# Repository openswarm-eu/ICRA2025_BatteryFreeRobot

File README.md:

# ICRA2025_Battery-Free Robot CapBot 

## Abstract

> Swarm robotics focuses on designing and coordinating large groups of relatively simple robots to perform tasks in a decentralised and collective manner.
> The swarm provides a resilient and flexible solution for many applications.
> However, contemporary swarm robots have a significant power problem in that secondary (i.e. rechargeable) batteries are slow to charge and offer lifetimes of only a few years, increasing maintenance costs and pollution due to battery replacement.
> We imagine a different future, wherein battery-free robots powered by supercapacitors can be recharged in seconds, offer long-life autonomous operation and can rapidly pass charge between one another using trophallaxis.
> In pursuit of this vision, we contribute the _CapBot_, a battery-free swarm robot equipped with Mecanum wheels, a Cortex-M4F application processor and Bluetooth Low Energy networking.
> CapBot  fully recharges in 16 s, offers 51 min of autonomous operation at top speed, and can transfer up to 50% of its available charge to a peer via trophallaxis in under 20 s.
> It is fully open-source: all software and hardware sources are available in this repository.

## Artefacts

### Hardware

CapBot's hardware is designed using KiCad, the design files are provided under [Hardware_Design](./Hardware_Design).

### Software

The [Software_Design](./Software_Design) folder contains an example using the CapBot Zephyr API.
The library itself is hosted at our [GitLab instance](https://gitlab.kuleuven.be/distrinet/taskforces/nes/capbot) and is included in this example using git submodules.

# CapBot ICRA demo

Fetch submodules:
```sh
git submodule update --init
```
Open workspace in [Visual Studio Code](https://code.visualstudio.com/):
```sh
code Software_Design
```
Make sure that the nRF Connect extension is installed according to the instructions at [Nordic's DevAcademy](https://academy.nordicsemi.com/courses/nrf-connect-sdk-fundamentals/lessons/lesson-1-nrf-connect-sdk-introduction/topic/exercise-1-1/)
Now, you should be able to open an nRF Connect terminal in Visual Studio Code. 
Next, execute [west](https://docs.nordicsemi.com/bundle/ncs-latest/page/zephyr/develop/west/index.html):
```sh
west build --build-dir build --board freebot-nrf52840 . -- -DBOARD_ROOT=.
```
This builds the demo project and creates a binary at `build/zephyr/zephyr.elf`.
[PyOCD](https://pyocd.io/) can then be used to flash the binary to the robot:
```sh
pyocd load -t nrf52840 build/zephyr/zephyr.hex
```

# Acknowledgement

Part of the source code in this repository is developed within the frame and for the purpose of the OpenSwarm project. This project has received funding from the European Unioan's Horizon Europe Framework Programme under Grant Agreement No. 101093046.

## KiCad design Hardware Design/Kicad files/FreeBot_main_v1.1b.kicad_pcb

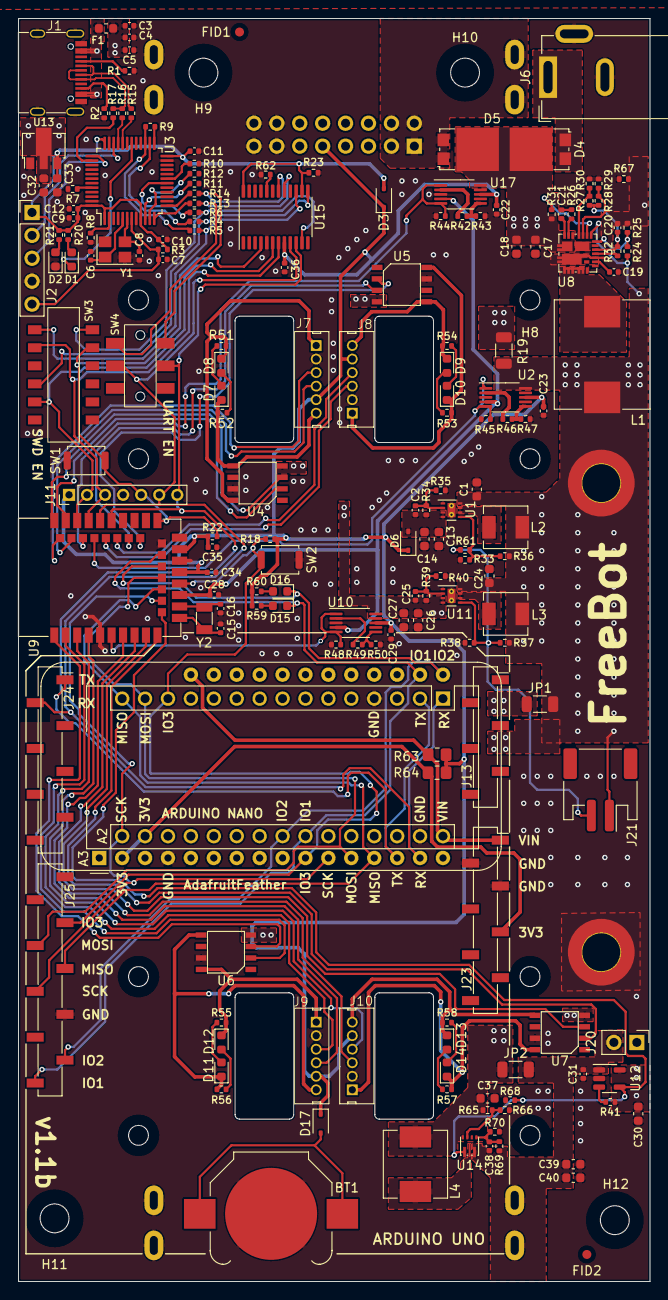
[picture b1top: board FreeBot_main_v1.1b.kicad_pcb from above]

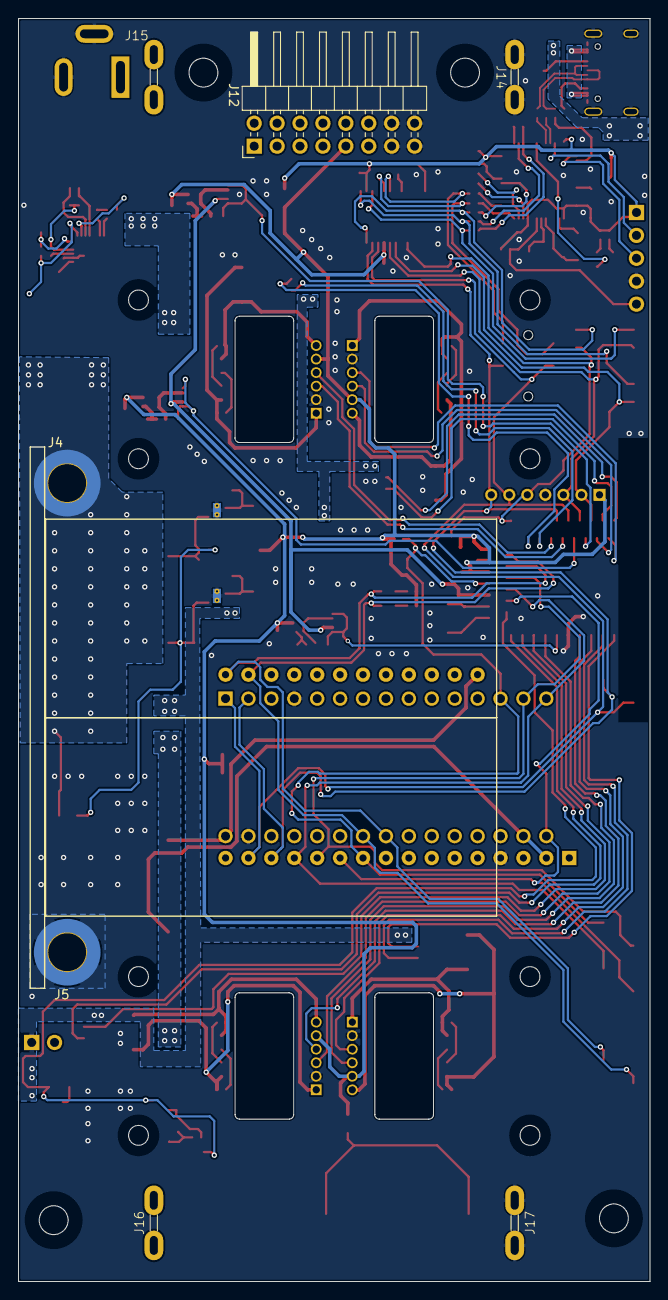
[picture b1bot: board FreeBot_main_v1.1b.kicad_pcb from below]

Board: 2 copper layers, 70.0 x 140.0 mm, 194 parts (7 on the bottom side), 126 nets.

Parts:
A2: Arduino_Nano_v3.x; Arduino_Nano
A3: Adafruit_Feather_Generic; Adafruit_Feather
BT1: Battery_Cell; BatteryHolder_Keystone_3000_1x12mm
C1, C24, C30, C32, C33, C37: 10uF; C_0603_1608Metric
C2, C25, C38: 10pF; C_0402_1005Metric
C3, C4, C5, C20: 1uF; C_0402_1005Metric
C6, C8: 22p; C_0402_1005Metric
C7, C9, C10, C11, C12, C21, C22, C23, C29, C31, C34, C35, C36: 0.1uF; C_0402_1005Metric
C13, C14, C17, C18, C26, C27, C39, C40: 22uF; C_0603_1608Metric
C15, C16: 12pF; C_0402_1005Metric
C19: 2.2uF; C_0402_1005Metric
C28: 0.01uF; C_0402_1005Metric
D1: Red; LED_0603_1608Metric
D2: Green; LED_0603_1608Metric
D3, D6, D17: CUS10S30,H3F; D_SOD-323
D4, D5: 10S45SP; TO-277A
D7, D10, D11, D14: GREEN LED NCD0603G1; LED_0603_1608Metric
D8, D9, D12, D13: RED LED NCD0603R1; LED_0603_1608Metric
D15, D16: 19-217/BHC-ZL1M2RY/3T; LED_0603_1608Metric
F1: S1206-F-6.0A; Fuse_0603_1608Metric
FID1, FID2: Fiducial; Fiducial_1mm_Mask2mm
H1, H2, H3, H4, H5, H6, H7, H8: MountingHole; MountingHole_2.2mm_M2_ISO7380
H9, H10, H11, H12: MountingHole; MountingHole_3.2mm_M3_ISO14580
J1: USB-type-c-16p; TYPE-C-31-M-12
J2: Conn_01x05; PinHeader_1x05_P2.54mm_Vertical
J4, J5: Conn_01x01; MountingHole_3.2mm_M3_Pad_TopBottom
J6: Barrel_Jack_MountingPin; BarrelJack_GCT_DCJ200-10-A_Horizontal
J7, J8, J9, J10: Conn_01x06; ZH-1.5mm-1x6p-TH
J11: Conn_01x07; PinHeader_1x07_P2.00mm_Vertical
J12: Conn_02x08_Odd_Even; PinHeader_2x08_P2.54mm_Horizontal
J13: Conn_01x06; PinSocket_1x06_P2.54mm_Vertical_SMD_Pin1Right
J14, J16: Conn_01x01; M3-side-terminal-DZ-32
J15, J17: Conn_01x01; M3-side-terminal-DZ-43
J20: Conn_01x02; PinHeader_1x02_P2.54mm_Vertical
J21: Conn_01x02; JST_PH_S2B-PH-SM4-TB_1x02-1MP_P2.00mm_Horizontal
J23, J24: Conn_01x08; PinSocket_1x08_P2.54mm_Vertical_SMD_Pin1Right
J25: Conn_01x10; PinSocket_1x10_P2.54mm_Vertical_SMD_Pin1Right
JP1, JP2: SolderJumper_2_Open; R_1206_3216Metric
L1: 300nH; L_Chilisin_BMRF00101040
L2, L3: 470nH FXL0420-R47-M; L_Sunlord_MWSA0412S
L4: 1uH FXL0630-1R0-M; L_Sunlord_MWSA0603S
R1, R2: 5.1k; R_0402_1005Metric
R3, R7, R18, R22, R27, R31, R32, R35, R36, R38, R40, R41, R44, R45, R48, R68, R70: 100k; R_0402_1005Metric
R4, R5, R6, R11, R12, R13, R14, R15, R16: 22; R_0402_1005Metric
R8: 10k DNP; R_0402_1005Metric
R9, R20, R52, R53, R56, R57, R59, R60: 100; R_0402_1005Metric
R10, R62, R66: 0; R_0402_1005Metric
R17: 1.5k; R_0402_1005Metric
R19: DNP; R_1206_3216Metric
R21, R51, R54, R55, R58: 27; R_0402_1005Metric
R23, R25, R43, R47, R50: 10k; R_0402_1005Metric
R24: 36.5k; R_0402_1005Metric
R26, R67: 1; R_0402_1005Metric
R28: 499k; R_0402_1005Metric
R29, R30, R33, R37, R61, R65: DNP; R_0402_1005Metric
R34: 348k; R_0402_1005Metric
R39: 316k; R_0402_1005Metric
R42, R46, R49: 390k; R_0402_1005Metric
R63, R64: R; R_0805_2012Metric_Pad1.20x1.40mm_HandSolder
R69: 806k; R_0402_1005Metric
SW1, SW2: TS-1088-AR02016; SW_Push_SPST_NO_Alps_SKRK
SW3: 4PDT-K3-2268S-F1
SW4: Switch-DPDT; DPDT-K3-2235S-F1
U1, U11: WSON-8-1EP_2x2mm_P0.5mm_EP0.9x1.6mm_ThermalVias
U2, U10, U17: TS5A23159DGS; VSSOP-10_3x3mm_P0.5mm
U3: STM32F103CBTx; LQFP-48_7x7mm_P0.5mm
U4, U5, U6, U7: BDR6120H; motor-driver-BDR6120H
U8: SIC431AED-T1-GE3; MLP44-24L SiC431
U9: E73-2G4M08S1C
U12: RT9742AGJ5F; TSOT-23-5
U13: HT7536-1; SOT-89-3
U14: boost-TPS61022; VQFN-HR-7 TPS61022
U15: TS3A27518EPW; TSSOP-24_4.4x7.8mm_P0.65mm
Y1: Crystal_GND24; Crystal_SMD_3225-4Pin_3.2x2.5mm
Y2: Q13FC1350000400; Crystal_SMD_3215-2Pin_3.2x1.5mm

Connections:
/USB-VDD: C9.1, C10.1, C11.1, C12.1, C33.1, D3.2 (A), J2.1, R3.2, R20.1, R21.1, R23.1, U3.1 (VBAT), U3.9 (VDDA), U3.24 (VDD), U3.36 (VDD), U3.48 (VDD), U13.3 (VOUT), U15.14 (IN2), U15.24 (IN1)
/Vbotin: D5.1 (A), D5.2 (A), J12.1, J12.2, J12.3, J12.4, J15.1
/Vbotout: C31.2, C38.2, C39.1, C40.1, J16.1, J20.2, JP2.2 (B), R69.1, U12.1 (VOUT), U14.3 (VOUT)
/Vmotor: C25.2, C26.1, C27.1, C30.1, J20.1, JP1.2 (B), R39.1, R41.1, U4.4 (VDD), U5.4 (VDD), U6.4 (VDD), U7.4 (VDD), U10.10, U11.3 (VOUT), U11.4 (VOUT), U12.5 (VIN)
/add-on-board/3V3: A2.17 (3V3), A3.2 (3V3), J23.5, R64.2
/add-on-board/VIN: A2.30 (VIN), A3.28 (VBAT), J23.1, R63.2
/add-on-board/addon-io.1: A2.24 (A5), A3.18 (SCL), D15.1 (K), J25.10, U9.22 (P0.07)
/add-on-board/addon-io.2: A2.23 (A4), A3.17 (SDA), D16.1 (K), J25.9, U9.20 (P0.12)
/add-on-board/addon-io.3: A2.13 (D10), A3.10 (A5), J25.3, R18.2, SW2.2, U9.17 (P1.09)
/add-on-board/addon-spi.miso: A2.15 (D12), A3.13 (MISO), J25.5, U9.16 (P0.08)
/add-on-board/addon-spi.mosi: A2.14 (D11), A3.12 (MOSI), J25.4, U9.18 (P0.04/AIN2)
/add-on-board/addon-spi.sck: A2.16 (D13), A3.11 (SCK), J25.6, U9.14 (P0.06)
/add-on-board/uart.rx: A2.1 (D1/TX), A3.15 (TX), J11.6, J24.2, SW4.5, U9.35 (P0.24), U15.9 (COM4)
/add-on-board/uart.tx: A2.2 (D0/RX), A3.14 (RX), J11.7, J24.1, SW4.2, U9.33 (P0.13), U15.10 (COM5)
/daplink/dap-inner-usb_N: R15.2, U3.32 (PA11)
/daplink/dap-inner-usb_P: R16.2, U3.33 (PA12)
/daplink/dap-led-red: D1.1 (K), U3.30 (PA9)
/daplink/dap-nrst: C7.1, J2.5, R3.1, U3.7 (NRST)
/daplink/dap-swclk: J2.3, U3.37 (PA14)
/daplink/dap-swdio: J2.2, U3.34 (PA13)
/daplink/dap-usbd_N: J1.A7 (DN1), J1.B7 (DN2), R15.1
/daplink/dap-usbd_P: J1.A6 (DP1), J1.B6 (DP2), R16.1, R17.2
/daplink/tgt-rx-dap: R13.2, SW4.4, U15.17 (NO4)
/daplink/tgt-swd-clk-dap: R4.1, SW3.10, U15.13 (NO2)
/daplink/tgt-swd-io-dap: R5.1, SW3.7, U15.15 (NO3)
/daplink/tgt-swd-rst-dap: R6.1, SW3.1, U15.11 (NO1)
/daplink/tgt-swd.clk: J11.2, SW3.11, U9.39 (SWDCLK), U15.6 (COM2)
/daplink/tgt-swd.io: J11.3, SW3.8, U9.37 (SWDIO), U15.7 (COM3)
/daplink/tgt-swd.rst: J11.5, R22.2, SW1.2, SW3.2, U9.26 (P0.18/RESET), U15.4 (COM1)
/daplink/tgt-tx-dap: R14.2, SW4.1, U15.18 (NO5)
/mcu/V-mea: C28.1, U2.4, U9.15 (P0.05/AIN3), U10.4, U17.4
/mcu/Vbotout-EN: R68.1, U9.12 (P0.26), U12.4 (EN), U14.1 (EN)
/mcu/Vcap-mea-en: R45.1, U2.1, U2.5, U9.36 (P1.00/SWO)
/mcu/Vin-mea-en: R44.1, U9.38 (P1.02-LS), U17.1, U17.5
/mcu/Vmotor-mea-en: R48.1, U9.6 (P1.13-LS), U10.1, U10.5
/mcu/m1-ctrl.in-a: U4.2 (INA), U9.41 (P0.09/NFC1-LS)
/mcu/m1-ctrl.in-b: U4.3 (INB), U9.43 (P0.10/NFC2-LS)
/mcu/m1-hall.c1: J7.4, U9.40 (P1.04-LS)
/mcu/m1-hall.c2: J7.3, U9.42 (P1.06-LS)
/mcu/m2-ctrl.in-a: U5.2 (INA), U9.28 (P0.15)
/mcu/m2-ctrl.in-b: U5.3 (INB), U9.30 (P0.17)
/mcu/m2-hall.c1: J8.4, U9.32 (P0.20)
/mcu/m2-hall.c2: J8.3, U9.34 (P0.22)
/mcu/m3-ctrl.in-a: U6.2 (INA), U9.2 (P1.10-LS)
/mcu/m3-ctrl.in-b: U6.3 (INB), U9.1 (P1.11-LS)
/mcu/m3-hall.c1: J9.4, U9.7 (P0.02/AIN1-LS)
/mcu/m3-hall.c2: J9.3, U9.3 (P0.03/AIN1-LS)
/mcu/m4-ctrl.in-a: U7.2 (INA), U9.10 (P0.30/AIN6-LS)
/mcu/m4-ctrl.in-b: U7.3 (INB), U9.9 (P0.31/AIN7-LS)
/mcu/m4-hall.c1: J10.4, U9.4 (P0.28/AIN4-LS)
/mcu/m4-hall.c2: J10.3, U9.8 (P0.29/AIN5-LS)
/pwr1/buck_en: R31.2, U8.19 (EN)
/pwr2/Vbotout-overcurr: R41.2, U12.3 (~FLG)
/pwr2/Vcap: C1.1, C24.1, C37.1, J4.1, J21.1, JP1.1 (A), JP2.1 (A), L1.2, L2.1, L3.1, L4.1, R19.2, R24.1, R36.1, R37.1, R65.1, U1.8 (VIN), U2.10, U8.18 (Vout), U11.8 (VIN), U14.7 (VIN)
/pwr2/Vcap_reg: C2.2, C13.1, C14.1, D6.2 (A), R34.1, U1.3 (VOUT), U1.4 (VOUT)
/pwr2/Vmotor-EN: J21.2, R37.2, R38.1, R61.2, U11.5 (EN)
GND: A2.4 (GND), A2.29 (GND), A3.4 (GND), BT1.2 (-), C1.2, C3.2, C4.2, C5.2, C6.2, C7.2, C8.2, C9.2, C10.2, C11.2, C12.2, C13.2, C14.2, C15.2, C16.2, C17.2, C18.2, C19.2, C20.2, C22.2, C23.2, C24.2, C26.2, C27.2, C28.2, C29.2, C30.2, C31.1, C32.2, C33.2, C34.2, C35.2, C36.1, C37.2, C39.2, C40.2, D2.1 (K), J1.0 (SH), J1.1 (SH), J1.2 (SH), J1.3 (SH), J1.A1 (GND), J1.A12 (GND), J1.B1 (GND), J1.B12 (GND), J2.4, J5.1, J6.2, J6.3 (MP), J7.2, J8.2, J9.2, J10.2, J11.4, J12.13, J12.14, J12.15, J12.16, J14.1, J17.1, J23.2, J23.3, J25.7, R1.2, R2.2, R7.2, R8.1, R10.1, R23.2, R25.2, R29.2, R30.2, R33.2, R35.2, R38.2, R40.2, R43.2, R44.2, R45.2, R47.2, R48.2, R50.2, R62.1, R66.2, R67.1, R67.2, R68.2, R70.2, SW1.1, SW2.1, U1.1 (AGND), U1.9 (PGND), U2.3 (GND), U3.8 (VSSA), U3.23 (VSS), U3.35 (VSS), U3.47 (VSS), U4.7 (GND), U5.7 (GND), U6.7 (GND), U7.7 (GND), U8.3 (Pgnd), U8.4 (Pgnd), U8.13 (Pgnd), U8.16 (Agnd), U8.25 (Agnd), U8.27 (Pgnd), U9.5 (GND), U9.21 (GND), U9.24 (GND), U10.3 (GND), U11.1 (AGND), U11.9 (PGND), U12.2 (GND), U13.1 (GND), U15.5 (GND), U17.3 (GND), Y1.2, Y1.4
unnamed: BT1.1 (+), D17.2 (A)
unnamed: C21.2, R26.2
unnamed: D1.2 (A), R20.2
unnamed: D2.2 (A), R21.2
unnamed: D4.1 (A), D4.2 (A), J6.1
unnamed: C17.1, C18.1, D4.3 (K), D5.3 (K), R19.1, R31.1, U8.1 (Vin), U8.2 (Vin), U8.22 (Vin), U8.26 (Vin), U17.10
unnamed: D7.2 (A), R51.2
unnamed: D7.1 (K), J7.6, R52.2, U4.5 (OUTB)
unnamed: D8.2 (A), R52.1
unnamed: D8.1 (K), J7.1, R51.1, U4.8 (OUTA)
unnamed: D9.2 (A), R53.2
unnamed: D9.1 (K), J8.6, R54.2, U5.5 (OUTB)
unnamed: D10.2 (A), R54.1
unnamed: D10.1 (K), J8.1, R53.1, U5.8 (OUTA)
unnamed: D11.2 (A), R55.2
unnamed: D11.1 (K), J9.6, R56.2, U6.5 (OUTB)
unnamed: D12.2 (A), R56.1
unnamed: D12.1 (K), J9.1, R55.1, U6.8 (OUTA)
unnamed: D13.2 (A), R57.2
unnamed: D13.1 (K), J10.6, R58.2, U7.5 (OUTB)
unnamed: D14.2 (A), R58.1
unnamed: D14.1 (K), J10.1, R57.1, U7.8 (OUTA)
unnamed: D15.2 (A), R59.2
unnamed: D16.2 (A), R60.2
unnamed: F1.1, J1.A4 (VBUS), J1.A9 (VBUS), J1.B4 (VBUS), J1.B9 (VBUS)
unnamed: J1.A5 (CC1), R1.1
unnamed: J1.B5 (CC2), R2.1
unnamed: L1.1, U8.5 (SW), U8.6 (SW), U8.7 (SW), U8.8 (SW), U8.9 (SW)
unnamed: L2.2, U1.6 (SW), U1.7 (SW)
unnamed: L3.2, U11.6 (SW), U11.7 (SW)
unnamed: R42.1, U17.2
unnamed: R42.2, R43.1, U17.6
unnamed: R46.1, U2.2
unnamed: R46.2, R47.1, U2.6
unnamed: R49.1, U10.2
unnamed: R49.2, R50.1, U10.6
unnamed: R33.1, R36.2, R61.1, U1.5 (EN)
unnamed: C2.1, R34.2, R35.1, U1.2 (FB)
unnamed: R7.1, U3.44 (BOOT0)
unnamed: R11.1, U3.10 (PA0)
unnamed: R12.1, U3.11 (PA1)
unnamed: R13.1, U3.12 (PA2)
unnamed: R14.1, U3.13 (PA3)
unnamed: R17.1, U3.38 (PA15)
unnamed: R6.2, U3.18 (PB0)
unnamed: R10.2, U3.19 (PB1)
unnamed: R9.2, U3.25 (PB12)
unnamed: R4.2, U3.26 (PB13)
unnamed: R5.2, R9.1, U3.27 (PB14)
unnamed: R8.2, U3.2 (PC13)
unnamed: C6.1, U3.5 (PD0), Y1.1
unnamed: C8.1, U3.6 (PD1), Y1.3
unnamed: R26.1, U8.23 (BOOT)
unnamed: R24.2, R25.1, U8.17 (FB)
unnamed: R27.2, R30.1, U8.21 (MODE1)
unnamed: R28.2, R29.1, U8.20 (MODE2)
unnamed: C21.1, U8.24 (PHASE)
unnamed: R32.2, U8.14 (Pgood)
unnamed: C20.1, R27.1, R28.1, R32.1, U8.15 (Vdd)
unnamed: C19.1, U8.12 (Vdrv)
unnamed: C15.1, U9.11 (P0.00/XL1), Y2.1
unnamed: C16.1, U9.13 (P0.01/XL2), Y2.2
unnamed: C25.1, R39.2, R40.1, U11.2 (FB)
unnamed: C38.1, R69.2, R70.1, U14.4 (FB)
unnamed: R65.2, R66.1, U14.6 (MODE)
unnamed: L4.2, U14.2 (SW)
unnamed: R62.2, U15.20 (~EN)
VBUS: C3.1, C4.1, C5.1, C32.1, F1.2, U13.2 (VIN)
VDD: C22.1, C23.1, C29.1, C34.1, C35.1, C36.2, D3.1 (K), D6.1 (K), D17.1 (K), J7.5, J8.5, J9.5, J10.5, J11.1, J12.9, R18.1, R22.1, R59.1, R60.1, R63.1, R64.1, U2.8 (VCC), U9.19 (VDD), U9.23 (VDDH), U10.8 (VCC), U15.8 (VCC), U17.8 (VCC)

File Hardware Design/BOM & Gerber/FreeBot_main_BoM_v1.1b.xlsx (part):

FreeBot_BoM
Source: | /Users/fan/work/projects/NetBot/FreeBot/FreeBot_v1.1/FreeBot_main/FreeBot_main_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
Date: | 2024 March 30, Tuesday 18:43:59
Tool: | Eeschema 7.0.5-0
Generator: | /Applications/KiCad/KiCad.app/Contents/SharedSupport/plugins/bom_csv_grouped_by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
Component Count: | 133
Ref | Qnty | Value | Part Nr | Footprint | Description | Vendor
A2 | 0 | DNP | Board layout | Arduino Nano
A3 | 0 | DNP | Board layout | Adafruit Feather
BT1 | 0 | DNP | Battery_Cell | Battery:BatteryHolder_Keystone_1058_1x2032 | Single-cell battery
C1, C24, C32, C33, C37 | 5 | 10uF | C | Capacitor_SMD:C_0603_1608Metric | Unpolarized capacitor
C2, C25, C38 | 3 | 10pF | C | Capacitor_SMD:C_0402_1005Metric | Unpolarized capacitor
C3, C4, C5, C20 | 4 | 1uF | C | Capacitor_SMD:C_0402_1005Metric | Unpolarized capacitor
C6, C8 | 2 | 22p | C | Capacitor_SMD:C_0402_1005Metric | Unpolarized capacitor
C7, C9, C10, C11, C12, C21, C22, C23, C29, C34, C35, C36 | 12 | 0.1uF | C | Capacitor_SMD:C_0402_1005Metric | Unpolarized capacitor
C13, C14, C17, C18, C26, C27, C39, C40 | 8 | 22uF | C | Capacitor_SMD:C_0603_1608Metric | Unpolarized capacitor
C15, C16 | 2 | 12pF | C | Capacitor_SMD:C_0402_1005Metric | Unpolarized capacitor
C19 | 1 | 2.2uF | C | Capacitor_SMD:C_0402_1005Metric | Unpolarized capacitor
C28 | 1 | 0.01uF | C | Capacitor_SMD:C_0402_1005Metric | Unpolarized capacitor
C30 | 0 | DNP | C | Capacitor_SMD:C_0603_1608Metric | Unpolarized capacitor
C31 | 0 | DNP | C | Capacitor_SMD:C_0402_1005Metric | Unpolarized capacitor
D1 | 1 | LED Red | NCD0603R1 | LED_SMD:LED_0603_1608Metric | Light emitting diode
D2 | 1 | LED Green | NCD0603G1 | LED_SMD:LED_0603_1608Metric | Light emitting diode
D3, D6, D17 | 3 | CUS10S30,H3F | 1N4148WS | Diode_SMD:D_SOD-323 | 75V 0.15A Fast switching Diode, SOD-323
D4, D5 | 2 | Schottky Rectifier Low VF Low IR | 10S45SP | Package_TO_SOT_SMD:TO-277A | 600V 6.0A Ultrafast Rectifier, TO-277A
D7, D10, D11, D14 | 0 | DNP | LED | LED_SMD:LED_0603_1608Metric | Light emitting diode
D8, D9, D12, D13 | 0 | DNP | LED | LED_SMD:LED_0603_1608Metric | Light emitting diode
D15, D16 | 2 | LED Blue | 19-217/BHC-ZL1M2RY/3T | LED_SMD:LED_0603_1608Metric | Light emitting diode
F1 | 1 | 0467002.NRHF | Fuse | Fuse:Fuse_0603_1608Metric | Fuse
FID1, FID2 | 0 | DNP | Fiducial | Fiducial:Fiducial_1mm_Mask2mm | Fiducial Marker
H1, H2, H3, H4, H5, H6, H7, H8 | 0 | DNP | MountingHole | MountingHole:MountingHole_2.2mm_M2_ISO7380 | Mounting Hole without connection
H9, H10, H11, H12 | 0 | DNP | MountingHole | MountingHole:MountingHole_3.2mm_M3_ISO14580 | Mounting Hole without connection
J1 | 1 | USB TYPE-C 16P | NCD0603G1 | Fan-socket-connector:TYPE-C-31-M-12
J2, J18 | 0 | DNP | Conn_01x05 | Connector_PinHeader_2.54mm:PinHeader_1x05_P2.54mm_Vertical | Generic connector, single row, 01x05, script generated (kicad-library-utils/sch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
J3 | 0 | DNP | Conn_01x04 | Connector_PinHeader_2.54mm:PinHeader_1x04_P2.54mm_Vertical | Generic connector, single row, 01x04, script generated (kicad-library-utils/sch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
J4, J5 | 2 | ROUND SPACER STEEL 2MM | 9774020960R (国产替代） | ROUND SPACER STEEL 2MM | ROUND SPACER STEEL 2MM | https://item.taobao.com/item.htm?_u=t2dmg8j26111&id=61450847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
J6 | 1 | Barrel_Jack_MountingPin | Barrel_Jack_MountingPin | Connector_BarrelJack:BarrelJack_GCT_DCJ200-10-A_Horizontal | DC Barrel Jack with a mounting pin
J7, J8, J9, J10 | 4 | ZH 1x6p1.5mm | ZH 1.5-6A | Fan-Connectors:ZH-1.5mm-1x6p-TH | Generic connector, single row, 01x06, script generated (kicad-library-utils/sch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
J11 | 0 | DNP | Conn_01x07 | Connector_PinHeader_2.00mm:PinHeader_1x07_P2.00mm_Vertical | Generic connector, single row, 01x07, script generated (kicad-library-utils/sch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
J12 | 0 | DNP | Conn_02x08_Odd_Even | Connector_PinHeader_2.54mm:PinHeader_2x08_P2.54mm_Horizontal | Generic connector, double row, 02x08, odd/even pin numbering scheme (row 1 odd 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
J13 | 0 | DNP | Conn_01x06 | Connector_PinHeader_2.54mm:PinHeader_1x06_P2.54mm_Vertical_SMD_Pin1Right
J14, J16 | 2 | DZ-32 | Conn_01x01 | Fan-Connectors:M3-side-terminal-DZ-32 | Generic connector, single row, 01x01, script generated (kicad-library-utils/sch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 | https://item.taobao.com/item.htm?_u=u2im4ruf08aa&id=52874775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
J15, J17 | 2 | DZ-43 | Conn_01x01 | Fan-Connectors:M3-side-terminal-DZ-43 | Generic connector, single row, 01x01, script generated (kicad-library-utils/sch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 | https://item.taobao.com/item.htm?_u=u2im4ruf08aa&id=52874775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
J19 | 0 | DNP | Conn_01x02 | Connector_PinHeader_2.54mm:PinHeader_1x02_P2.54mm_Vertical | Generic connector, single row, 01x02, script generated (kicad-library-utils/sch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
J21 | 1 | HDGC2001WR-S-2P | Conn_01x03 | Connector_JST:JST_PH_S2B-PH-SM4-TB_1x02-1MP_P2.00mm_Horizontal
J23, J24 | 0 | DNP | Conn_01x08 | Connector_PinHeader_2.54mm:PinHeader_1x08_P2.54mm_Vertical_SMD_Pin1Right
J25 | 0 | DNP | Conn_01x10 | Connector_PinHeader_2.54mm:PinHeader_1x10_P2.54mm_Vertical_SMD_Pin1Right
L1 | 1 | 300nH | FXL1040-R30-M | Inductor_SMD:L_Chilisin_BMRF00101040 | Inductor
L2, L3 | 2 | 470nH | FXL0420-R47-M | Inductor_SMD:L_Sunlord_MWSA0412S | Inductor
L4 | 1 | 1uH | FXL0630-1R0-M | Inductor_SMD:L_Sunlord_MWSA0603S | Inductor
R1, R2 | 2 | 5.1k | R | Resistor_SMD:R_0402_1005Metric | Resistor
R3, R7, R18, R22, R27, R31, R32, R35, R36, R38, R40, R44, R45, R48, R68, R70 | 16 | 100k | R | Resistor_SMD:R_0402_1005Metric | Resistor
R4, R5, R6, R11, R12, R13, R14, R15, R16 | 9 | 22 | R | Resistor_SMD:R_0402_1005Metric | Resistor
R8, R29, R30, R33, R37, R41, R51, R52, R53, R54, R55, R56, R57, R58, R61, R65 | 0 | DNP | R | Resistor_SMD:R_0402_1005Metric | Resistor
R9, R20, R59, R60 | 4 | 100 | R | Resistor_SMD:R_0402_1005Metric | Resistor
R10, R62, R66 | 3 | 0 | R | Resistor_SMD:R_0402_1005Metric | Resistor
R17 | 1 | 1.5k | R | Resistor_SMD:R_0402_1005Metric | Resistor
R19 | 0 | DNP | R | Resistor_SMD:R_1206_3216Metric | Resistor
R21 | 1 | 27 | R | Resistor_SMD:R_0402_1005Metric | Resistor
R23, R25, R43, R47, R50 | 5 | 10k | R | Resistor_SMD:R_0402_1005Metric | Resistor
R24 | 1 | 36.5k | R | Resistor_SMD:R_0402_1005Metric | Resistor
R26, R67 | 2 | 1 | R | Resistor_SMD:R_0402_1005Metric | Resistor
R28 | 1 | 499k | R | Resistor_SMD:R_0402_1005Metric | Resistor
R34 | 1 | 348k | R | Resistor_SMD:R_0402_1005Metric | Resistor
R39 | 1 | 316k | R | Resistor_SMD:R_0402_1005Metric | Resistor
R42, R46, R49 | 3 | 390k | R | Resistor_SMD:R_0402_1005Metric | Resistor
R69 | 1 | 806k | R | Resistor_SMD:R_0402_1005Metric | Resistor
R63, R64 | 0 | DNP | R | Resistor_SMD:R_0805_2012Metric_Pad1.20x1.40mm_HandSolder | Resistor
SW1, SW2 | 2 | SW_Push | TS-1088-AR02016 | Button_Switch_SMD:SW_Push_SPST_NO_Alps_SKRK | Push button switch, generic, two pins
SW3 | 0 | DNP | Switch-4PDT | Fan-switch:4PDT-K3-2268S-F1
SW4 | 0 | DNP | Switch-DPDT | Fan-switch:DPDT-K3-2235S-F1
U1, U11 | 2 | Boost DCDC | TPS61021ADSGR | Package_SON:WSON-8-1EP_2x2mm_P0.5mm_EP0.9x1.6mm_ThermalVias
U2 | 1 | SPDT analog switch | TS5A23159DGSR | Package_SO:VSSOP-10_3x3mm_P0.5mm | Dual SPDT 1ohm Bidirectional Analog Switch with Off protection, VSSOP-10
U3 | 1 | STM32F103CBTx | STM32F103CBT6 | Package_QFP:LQFP-48_7x7mm_P0.5mm | STMicroelectronics Arm Cortex-M3 MCU, 128KB flash, 20KB RAM, 72 MHz, 2.0-3.6V, 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
U4, U5, U6, U7 | 4 | Motor-driver-1ch | BDR6120H | Fan-Motor:motor-driver-BDR6120H
U8 | 1 | Buck SIC431 | SIC431BED-T1-GE3 | Fan-pwr:MLP44-24L SiC431
U9 | 1 | RF Module | E73-2G4M08S1C | Fan-MCU-Library:E73-2G4M08S1C
U10, U17 | 0 | DNP | TS5A23159DGSR | Package_SO:VSSOP-10_3x3mm_P0.5mm | Dual SPDT 1ohm Bidirectional Analog Switch with Off protection, VSSOP-10
U12 | 0 | DNP | RT9742AGJ5F | Package_TO_SOT_SMD:TSOT-23-5 | 3A, Discharge, Active High EN, TSOT-23-5
U13 | 1 | 100mA Voltage Regulator | HT7536-1 | Package_TO_SOT_SMD:SOT-89-3 | 100mA Low Dropout Voltage Regulator, Fixed Output, SOT89
U14 | 1 | Boost DCDC | TPS61022RWUR | VQFN7_2x2 | 8-A boost converter with 0.5-V ultra-low input voltage in a VQFN-HR (RWU) packa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

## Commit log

2024-09-13 Create Schematic
2024-09-13 Create KICAD project files
2024-09-24 Refactor readme file names
2024-09-24 Rename root folders
2024-09-24 Add preliminary demo
2024-09-26 Add root readme
2024-09-26 Update root readme
2025-10-01 readme: adding ack
2025-10-01 readme: fixing ack
